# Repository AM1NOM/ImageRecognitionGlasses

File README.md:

# IMAGE RECOGNITION GLASSES

We are aiming to build a device that can help blind people be aware of their surroundings, using a camera, image recognition, and text-to-speech. There are several stages involved in building the device, including designing the hardware and developing the software.
You can find our Word document about this project [here](https://mercialt-my.sharepoint.com/:w:/g/personal/bahramia_mercia_school/IQDaSRObkFn9QrRjMxeWHlX-AcOBT_vHGkkaOwhr4ABxG9w?e=yJghnD).

## Screenshots

- **Schematic:**

- **PCB:**

- **CAD:**

## Bill of Materials (BOM)

| Part Name                             | Reason / Description                                       | Quantity | Unit Price (£) | Seller (Direct Product Link)                                                        | Notes                             |
| ------------------------------------- | ---------------------------------------------------------- | -------- | -------------- | ----------------------------------------------------------------------------------- | --------------------------------- |
| Raspberry Pi 5 (8GB)                  | Main processing computer running software and camera tasks | 1        | 120.00     | [The Pi Hut](https://thepihut.com/products/raspberry-pi-5?variant=42531604955331)     | Official UK Raspberry Pi reseller |
| PiSugar 3                             | Battery                                                    | 1        | 39.99          | [Amazon](https://www.amazon.co.uk/Portable-Pwnagotchi-Raspberry-Accessories-handhold/dp/B09QS12N1W/ref=asc_df_B09QS12N1W?tag=googshopuk-21&linkCode=df0&hvadid=697193037966&hvpos=&hvnetw=g&hvrand=10037452718169759682&hvpone=&hvptwo=&hvqmt=&hvdev=c&hvdvcmdl=&hvlocint=&hvlocphy=9199185&hvtargid=pla-1655574045587&psc=1&hvocijid=10037452718169759682-B09QS12N1W-&hvexpln=0&gad_source=1)  | Pi compatible UPS                 |
| Samsung EVO Select 128GB microSD (A2) | Operating system and storage                               | 1        | 11.99          | [Amazon](https://www.amazon.co.uk/dp/B09FFD6R2B)                                    | High endurance storage            |
| Raspberry Pi Screw & Standoff Kit     | Mounting hardware for assembly                             | 1        | 9.99           | [Amazon](https://www.amazon.co.uk/dp/B07D7828LC)                                    | M2.5 compatible                   |
| 4-Way Straight Pin                       | Electrical interface for peripheral modules                | 1        | 3.15           | [Amazon](https://www.amazon.co.uk/4-Way-Straight-Header-2-54mm-Circuit/dp/B0BX3Z9GNS/ref=asc_df_B0BX3Z9GNS?mcid=57455ceec2803d30b4b1c32e860aff6e&tag=googshopuk-21&linkCode=df0&hvadid=718893858868&hvpos=&hvnetw=g&hvrand=9388150854418113669&hvpone=&hvptwo=&hvqmt=&hvdev=c&hvdvcmdl=&hvlocint=&hvlocphy=9199185&hvtargid=pla-2400500014768&psc=1&hvocijid=9388150854418113669-B0BX3Z9GNS-&hvexpln=0&gad_source=1)                                   | Male      |
| JST-PH 4-pin Cable                    | Cable between Raspberry Pi GPIO and custom PCB             | 1        | 1.00           | [The Pi Hut](https://thepihut.com/products/2-0mm-pitch-4-pin-cable-matching-pair-jst-ph-compatible?variant=40200490647747&country=GB&currency=GBP&utm_source=chatgpt.com)                                               | 2.0 mm pitch JST PH cable    |
| Tactile Switch                     | User input/buttons                                         | 3        | 3.19           | [Amazon](https://www.amazon.co.uk/YPBEW-Mechanical-Keyboard-Replacement-Accessory/dp/B0D3J3CS3C/ref=asc_df_B0D3J3CS3C?mcid=90a114b67512386dbadf56baa321a542&tag=googshopuk-21&linkCode=df0&hvadid=710855216590&hvpos=&hvnetw=g&hvrand=2885919442907818046&hvpone=&hvptwo=&hvqmt=&hvdev=c&hvdvcmdl=&hvlocint=&hvlocphy=9199185&hvtargid=pla-2362732486251&psc=1&hvocijid=2885919442907818046-B0D3J3CS3C-&hvexpln=0&gad_source=1)                                  | Momentary push-button             |
| 470Ω 0603 Resistor                 | Current limiting or signal conditioning                    | 3        | 3.45           |[ [Amazon](https://www.amazon.co.uk/UMTMedia®-30pcs-470K-ohm-Electronic/dp/B09DCCF7SW/ref=asc_df_B09DCCF7SW?mcid=309e09b5b18b3172b1bbde5f23984672&tag=googshopuk-21&linkCode=df0&hvadid=710804269330&hvpos=&hvnetw=g&hvrand=2627136518115524604&hvpone=&hvptwo=&hvqmt=&hvdev=c&hvdvcmdl=&hvlocint=&hvlocphy=9199185&hvtargid=pla-2399134325642&hvocijid=2627136518115524604-B09DCCF7SW-&hvexpln=0&gad_source=1&th=1)                                 | Standard SMD resistor             |
| Raspberry Pi 5 Active Cooler          | Prevents thermal throttling during heavy workloads         | 1        | 9.60           | [The Pi Hut](https://thepihut.com/products/active-cooler-for-raspberry-pi-5)                        | Official cooler              |
| M2.5 Screw Assortment Pack            | Hardware for mounting boards, PCBs, and standoffs          | 1        | 4.80           | [The Pi Hut](https://thepihut.com/products/adafruit-black-nylon-screw-and-stand-off-set-m2-5-thread)| Nylon screw & standoff kit   
| USB Webcam  | Small camera for video input     |        1 |    18.10 |[Amazon](https://www.amazon.co.uk/innomaker-Computer-Raspberry-Supports-Windows/dp/B0CNCSFQC1/ref=asc_df_B0CNCSFQC1?mcid=6a5f1bcbfa9733429b3220cdf497f310&tag=googshopuk-21&linkCode=df0&hvadid=696386561233&hvpos=&hvnetw=g&hvrand=3702107595903094867&hvpone=&hvptwo=&hvqmt=&hvdev=c&hvdvcmdl=&hvlocint=&hvlocphy=9199185&hvtargid=pla-2309316011891&psc=1&hvocijid=3702107595903094867-B0CNCSFQC1-&hvexpln=0&gad_source=1) | a compact 1080p model                                 |
| USB Headset | Audio output for listening/calls |        1 |    5.99 | [Amazon](https://www.amazon.co.uk/Headphones-Microphone-Wired-Cancelling-Business-black/dp/B0FLDVP4GD/ref=asc_df_B0FLDVP4GD?mcid=395dca7f5b063f17ad818a3d6d89ce47&tag=googshopuk-21&linkCode=df0&hvadid=758428357322&hvpos=&hvnetw=g&hvrand=5466172132595335940&hvpone=&hvptwo=&hvqmt=&hvdev=c&hvdvcmdl=&hvlocint=&hvlocphy=9199185&hvtargid=pla-2448953799310&psc=1&hvocijid=5466172132595335940-B0FLDVP4GD-&hvexpln=0&gad_source=1)    | headphones |
|YSJJZRL USB to PH2.0 Cable | Cable to connect USB ports to PH2.0 peripheral board |        1 |         £4.98 | [Amazon](https://www.amazon.co.uk/dp/B0CSPHTRZY) | USB 2.0 data + power, 1.5 m, PH2.0 female |

For the complete, raw BOM file see [BOM.csv](BOM.csv).

## Firmware
Firmware and microcontroller code are in `CODE/Firmware.py`.

## Other files
- PCB and schematic files: [PCB/hackpad.kicad_pcb](PCB/hackpad.kicad_pcb)
- PCB project files and library: `PCB/` folder
- 3D models for case: `CAD/` folder

## License
This project is open-source.

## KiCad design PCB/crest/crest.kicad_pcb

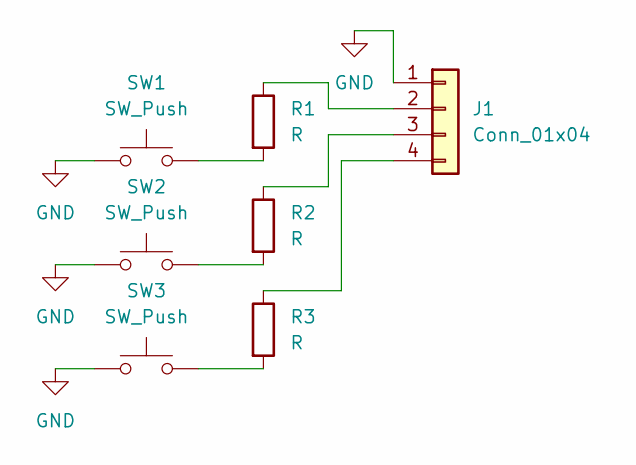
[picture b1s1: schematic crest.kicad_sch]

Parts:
J1: Conn_01x04; JST_PH_B4B-PH-K_1x04_P2.00mm_Vertical
R1, R2, R3: R; R_0603_1608Metric
SW1, SW2, SW3: SW_Push; SW_Cherry_MX_1.00u_PCB

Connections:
GND: J1.1, SW1.1, SW2.1, SW3.1
unnamed: J1.2, R1.1
unnamed: J1.3, R2.1
unnamed: J1.4, R3.1
unnamed: R1.2, SW1.2
unnamed: R2.2, SW2.2
unnamed: R3.2, SW3.2

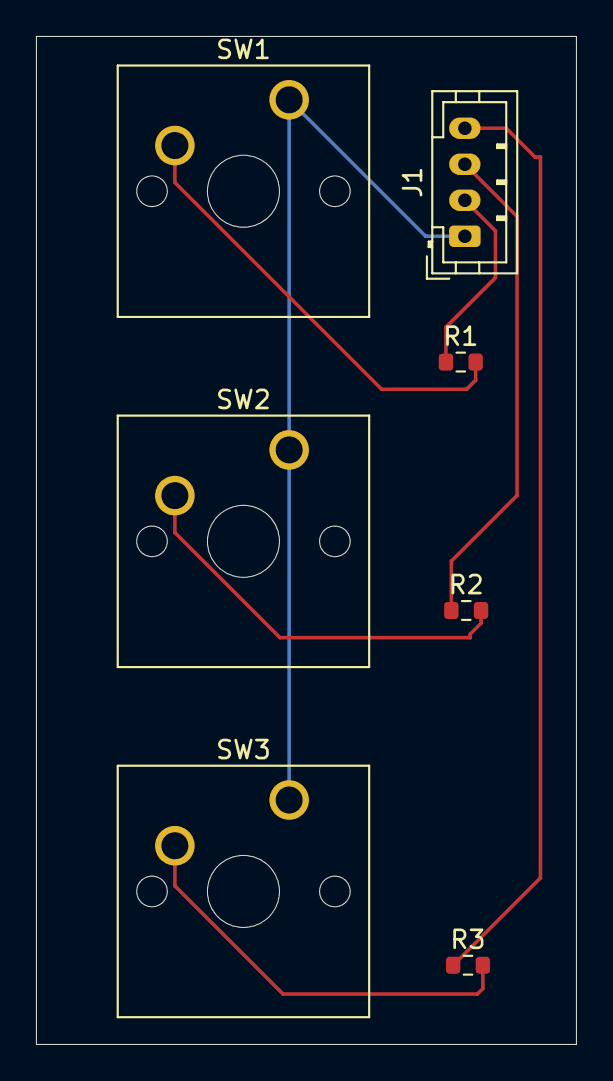
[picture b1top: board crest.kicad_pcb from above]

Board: 2 copper layers, 30.0 x 56.0 mm, 7 parts (0 on the bottom side), 7 nets.

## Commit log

2026-03-23 Add hardware components list for project
2026-03-23 Add parts list for Raspberry Pi project
    Added a detailed parts list with descriptions, quantities, prices, and links for a Raspberry Pi project.
2026-03-23 Update hardware list in README.md
    Replaced Waveshare UPS HAT and Momentary Push Button Switch with PiSugar 3 and updated links.
2026-03-23 Fix formatting and update product links in README
2026-03-23 Remove optional components from README
    Removed several optional components from the list, including mounting tape, camera lens cover, Bluetooth adapter, screw assortments, jumper wires, heat shrink tubing, PETG filament, rubber feet, and 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
2026-03-23 Update component list in README.md
    Added new components for Raspberry Pi 5 project including active cooler, M2.5 screw assortment, and connectors.
2026-03-23 Revise components list and update prices
    Updated pricing and added new items including USB Webcam, USB Headset, and USB to PH2.0 Cable.
2026-03-23 Update prices and links in README.md
    Updated the price of the Raspberry Pi 5 and corrected the link formatting. Adjusted the price of the USB to PH2.0 Cable.
2026-03-23 Update prices for Raspberry Pi components in README
2026-03-23 Revise parts list with updated prices and new items
    Updated prices and added new components to the parts list.
2026-03-23 Revise component listings and pricing in README
    Updated product details and prices for various components in the README.
2026-03-23 Modify Tactile Switch entry in README
    Updated the price and link for the Tactile Switch.
2026-03-23 Add BOM.csv for Raspberry Pi project components
    Added a Bill of Materials (BOM) for the Raspberry Pi project, including part names, descriptions, quantities, prices, and seller links.
2026-03-23 Enhance README with project details and resources
    Added detailed project description, features, screenshots, bill of materials, firmware, and other files sections to the README.
2026-03-23 Fix image paths in README.md
    Updated image references in the README file for schematic and PCB.
2026-03-23 Fix image link for schematic in README
2026-03-24 Add firmware for button keycode functionality
    Implement button press detection to send keycodes.
2026-03-24 Rename importcv2.py to CODE/importcv2.py
2026-03-29 Rename Assembly 1.stl to CAD/Assembly 1.stl
2026-03-29 Update README with project document link
    Added link to project Word document in README.
2026-03-29 Update project document link in README
2026-03-29 Remove Features section from README
    Removed the Features section from the README.
2026-03-29 Update firmware file path in README
2026-03-29 Rename Assembly 3.stl to 1.stl
2026-03-29 Rename Assembly 1.stl to 2.stl
2026-03-29 Rename Assembly 4.stl to 3.stl
2026-04-23 Implement EncoderCNN and DecoderRNN classes
2026-04-23 Add training script for image captioning
    Implement training loop for image captioning model with a dummy dataset.
2026-04-23 Add README for image captioning mini model
    Adds a README for the image captioning mini model, detailing the encoder and decoder used, along with instructions for running training.
2026-04-23 Refactor dataset handling for CIFAR-10 captions
2026-04-23 Update DecoderRNN to project features into LSTM state
    Refactor DecoderRNN to initialize LSTM state from image features.
